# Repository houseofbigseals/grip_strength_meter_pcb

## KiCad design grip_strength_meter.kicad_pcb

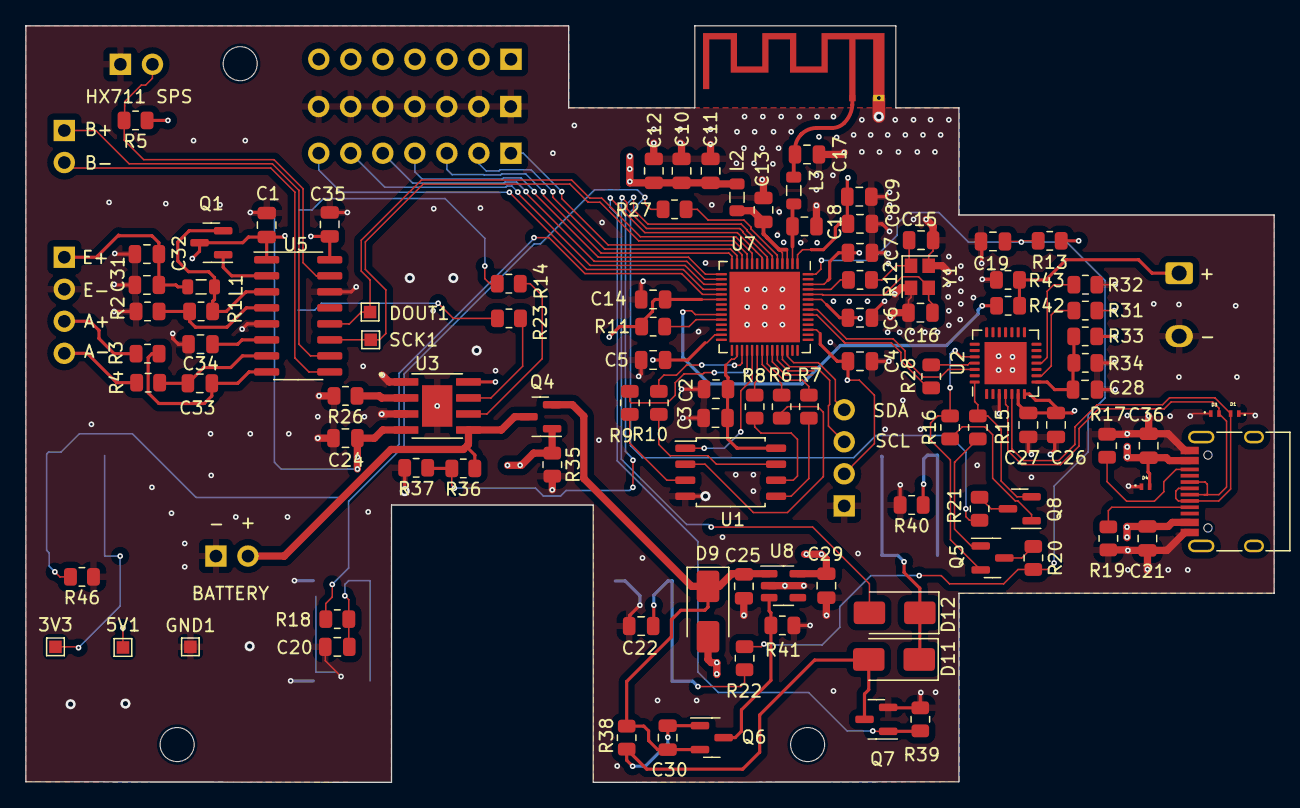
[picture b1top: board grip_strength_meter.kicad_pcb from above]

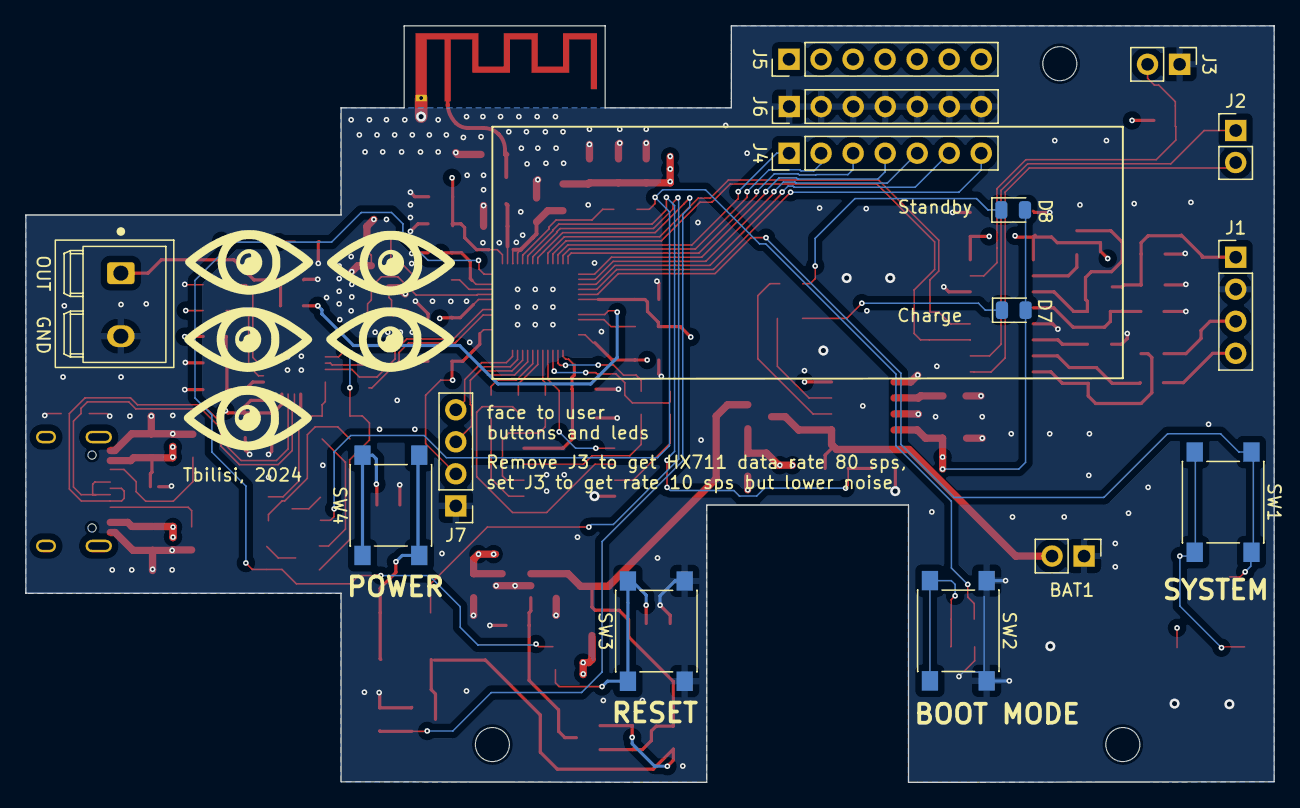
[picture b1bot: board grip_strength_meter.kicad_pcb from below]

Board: 4 copper layers, 99.0 x 60.0 mm, 122 parts (15 on the bottom side), 83 nets.

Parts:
3V3, 5V1: TestPoint; TestPoint_Pad_1.0x1.0mm
AE2: Antenna_Chip; Texas_SWRA117D_2.4GHz_Left
BAT1: Conn_01x02_Pin; PinHeader_1x02_P2.54mm_Vertical
C1, C2, C4, C5, C6, C7, C8, C11, C13, C14, C26, C30, C31, C33, C34: 100nF; C_0805_2012Metric
C3, C9, C10, C19: 1uF; C_0805_2012Metric
C12, C24, C28, C32, C35: 10uF; C_0805_2012Metric
C15, C16: 10pF; C_0805_2012Metric
C17: 1.2pF; C_0805_2012Metric
C18: 1.8pF; C_0805_2012Metric
C20, C22: 100 nF; C_0805_2012Metric
C21, C36: 5uF; C_0805_2012Metric
C25, C29: 2uF; C_0805_2012Metric
C27: 4.7uF; C_0805_2012Metric
D1, D3, D4: H5VL10B; DIODFN2_98X58X50L26X51N
D7: RED LED; LED_0805_2012Metric
D8: GREEN LED; LED_0805_2012Metric
D9, D11, D12: SS54; D_SMA
DOUT1: TestPoint; TestPoint_Pad_1.0x1.0mm
GND1: TestPoint; TestPoint_Pad_1.0x1.0mm
H1, H2, H3: MountingHole; MountingHole_2.7mm_M2.5_ISO7380
J1: Conn_01x04_Male; PinHeader_1x04_P2.54mm_Vertical
J2, J3: Conn_01x02_Male; PinHeader_1x02_P2.54mm_Vertical
J4, J5, J6: Conn_01x07_Pin; PinHeader_1x07_P2.54mm_Vertical
J7: Conn_01x04_Pin; PinHeader_1x04_P2.54mm_Vertical
L1: 3.3uH; L_0805_2012Metric
L2: 2nH; L_0805_2012Metric
L3: 2.4nH; L_0805_2012Metric
OUTPUT1: Screw_Terminal_01x02; screw-2-pin
Q1: SS8550; SOT-23
Q4, Q6: AO3401A; SOT-23
Q5, Q8: MMBT3904; SOT-23
Q7: AO3400A; SOT-23
R1, R5: 20K; R_0805_2012Metric
R2: 8.2K; R_0805_2012Metric
R3, R4, R40: 100R; R_0805_2012Metric
R6, R7, R8, R9, R10, R12, R18, R20, R21, R22: 0R; R_0805_2012Metric
R11, R13, R15, R16, R32, R36, R43, R46: 10K; R_0805_2012Metric
R14, R23: 1K; R_0805_2012Metric
R17, R19: 5K1; R_0805_2012Metric
R26: 1K5; R_0805_2012Metric
R27: 22R; R_0805_2012Metric
R28: 499R; R_0805_2012Metric
R31: 4K7; R_0805_2012Metric
R33: 24K; R_0805_2012Metric
R34: 47K; R_0805_2012Metric
R35, R38, R41: 100K; R_0805_2012Metric
R37, R42: 30K; R_0805_2012Metric
R39: 1M; R_0805_2012Metric
SCK1: TestPoint; TestPoint_Pad_1.0x1.0mm
SW1, SW2, SW3, SW4: SW_DPST; SW_Push_1P1T_NO_6x6mm_H9.5mm
U1: W25Q128JVS; SOIC-8_5.23x5.23mm_P1.27mm
U2: CP2102; QFN-28-1EP_5x5mm_P0.5mm_EP3.35x3.35mm
U3: TP4056; SOP127P600X175-9N
U5: HX711; SOP-16_3.9x9.9mm_P1.27mm
U7: ESP32-S2; QFN-56-1EP_7x7mm_P0.4mm_EP5.6x5.6mm
U8: TLV75733PDBV; SOT-23-5
USBC1: USB_C_Receptacle_USB2.0; USB_C_Receptacle_HRO_TYPE-C-31-M-12
Y1: Crystal_GND24; Crystal_SMD_2520-4Pin_2.5x2.0mm

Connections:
/3V3: 3V3.1, C1.1, C4.1, C5.1, C6.1, C7.1, C8.1, C9.1, C10.1, C11.1, C12.1, C14.1, C26.1, C27.1, C29.1, C35.1, J5.1, J5.2, J5.3, J5.4, J5.5, J5.6, J5.7, J7.2, L2.2, Q1.3 (E), R5.1, R11.2, R13.2, R31.1, SW1.2, U2.6 (VDD), U2.7 (VREGIN), U5.1 (VSUP), U5.16 (DVDD), U7.1 (VDDA), U7.20 (VDD3P3_RTC), U7.27 (VDD3P3_RTC_IO), U7.45 (VDD3P3_CPU), U7.51 (VDDA), U7.54 (VDDA), U8.5 (OUT)
/5V_USB: 5V1.1, C21.1, C24.1, C36.1, D4.2 (A2), D7.2 (A), D8.2 (A), D9.2 (A), Q4.1 (G), R33.2, R35.1, U3.4 (VCC), U3.8 (CE), USBC1.A4 (VBUS), USBC1.A9 (VBUS), USBC1.B4 (VBUS), USBC1.B9 (VBUS)
/CP2102_RX: R28.2, U2.25 (RXD)
/CP2102_TX: U2.26 (TXD), U7.49 (U0RXD/GPIO44)
/DOUT: DOUT1.1, U5.12 (DOUT), U7.10 (GPIO5/ADC1_CH4)
/DTR: Q8.2 (E), R15.2, U2.28 (~DTR)
/GPIO_BUTTON_CHECK: D12.2 (A), U7.7 (GPIO2/ADC1_CH1)
/GPIO_POWEROFF: Q7.1 (G), R39.1, U7.8 (GPIO3/ADC1_CH2)
/PD_SCK: SCK1.1, U5.11 (PD_SCK), U7.11 (GPIO6/ADC1_CH5)
/RTS: Q5.2 (E), R16.2, U2.24 (~RTS)
/V_BAT_MEASURE: R36.2, R37.1, U7.6 (GPIO1/ADC1_CH0)
/mcu_buttons_leds/CHIP_EN: C19.1, R13.1, R20.2, R22.2, U7.56 (CHIP_PU/RESET)
/mcu_buttons_leds/CIO0_BTN: R18.2, R21.2, R27.1
/mcu_buttons_leds/DAC_OUT: OUTPUT1.1, R42.2, R43.2
/mcu_buttons_leds/GPIO7: J4.1, U7.12 (GPIO7/ADC1_CH6)
/mcu_buttons_leds/GPIO8: J4.2, U7.13 (GPIO8/ADC1_CH7)
/mcu_buttons_leds/GPIO9: J4.3, U7.14 (GPIO9/ADC1_CH8)
/mcu_buttons_leds/GPIO10: J4.4, U7.15 (GPIO10/ADC1_CH9)
/mcu_buttons_leds/GPIO11: J4.5, U7.16 (GPIO11/ADC2_CH0)
/mcu_buttons_leds/GPIO12: J4.6, U7.17 (GPIO12/ADC2_CH1)
/mcu_buttons_leds/GPIO13: J4.7, U7.18 (GPIO13/ADC2_CH2)
/mcu_buttons_leds/GPIO14: R46.2, SW1.1, U7.19 (GPIO14/ADC2_CH3)
/mcu_buttons_leds/GPIO35: J7.3, U7.39 (GPIO35)
/mcu_buttons_leds/GPIO36: J7.4, U7.40 (GPIO36)
/mcu_buttons_leds/VDD_SPI: C2.1, C3.1, U1.8 (VCC), U7.30 (VDD_SPI)
/tp4056/POWER_EN: Q6.3 (D), R41.1, U8.3 (EN)
/tp4056/V_BAT: BAT1.2, Q4.3 (D), R36.1, U3.5 (BAT)
/usb_cp2102/USB_N: D1.2 (A2), U2.5 (D-), USBC1.A7 (D-), USBC1.B7 (D-)
/usb_cp2102/USB_P: D3.2 (A2), U2.4 (D+), USBC1.A6 (D+), USBC1.B6 (D+)
GND: AE2.2 (GND), BAT1.1, C1.2, C2.2, C3.2, C4.2, C5.2, C6.2, C7.2, C8.2, C9.2, C10.2, C11.2, C12.2, C13.2, C14.2, C15.2, C16.2, C17.2, C18.2, C19.2, C20.1, C21.2, C22.1, C24.2, C25.2, C26.2, C27.2, C28.2, C29.2, C31.2, C32.2, C34.2, C35.2, C36.2, D1.1 (A1), D3.1 (A1), D4.1 (A1), GND1.1, J1.2, J3.1, J6.1, J6.2, J6.3, J6.4, J6.5, J6.6, J6.7, J7.1, OUTPUT1.2, Q7.2 (S), R2.2, R17.2, R19.2, R26.2, R32.2, R34.1, R35.2, R37.2, R39.2, R40.2, R41.2, R43.1, R46.1, SW2.1, SW3.2, U1.4 (GND), U2.3 (GND), U2.29 (GND), U3.1 (TEMP), U3.3 (GND), U3.9 (EP), U5.5 (AGND), U5.14 (XI), U7.57 (GND), U8.2 (GND), USBC1.A1 (GND), USBC1.A12 (GND), USBC1.B1 (GND), USBC1.B12 (GND), Y1.2, Y1.4
unnamed: AE2.1 (FEED), C17.1, L3.1
unnamed: C13.1, L2.1, U7.3 (VDD3P3), U7.4 (VDD3P3)
unnamed: C15.1, R12.1, Y1.1
unnamed: C20.2, R18.1, SW2.2
unnamed: C22.2, R22.1, SW3.1
unnamed: D7.1 (K), R23.1
unnamed: D8.1 (K), R14.1
unnamed: C30.2, D11.2 (A), Q6.1 (G), Q7.3 (D), R38.2
unnamed: D11.1 (K), D12.1 (K), SW4.2
unnamed: C31.1, C32.1, J1.1, L1.1
unnamed: J1.3, R3.2
unnamed: J1.4, R4.2
unnamed: J2.1, U5.10 (INB+)
unnamed: J2.2, U5.9 (INB-)
unnamed: J3.2, R5.2, U5.15 (RATE)
unnamed: Q1.1 (B), U5.2 (BASE)
unnamed: L1.2, Q1.2 (C), R1.1, U5.3 (AVDD)
unnamed: Q5.1 (B), R15.1
unnamed: Q5.3 (C), R20.1
unnamed: Q8.1 (B), R16.1
unnamed: Q8.3 (C), R21.1
unnamed: R40.1, SW4.1
unnamed: R8.1, U1.6 (CLK)
unnamed: R7.1, U1.5 (DI(IO0))
unnamed: R6.1, U1.2 (DO(IO1))
unnamed: R9.1, U1.3 (IO2)
unnamed: R10.1, U1.7 (IO3)
unnamed: U1.1 (~CS), U7.33 (SPICS0/GPIO29)
unnamed: C28.1, R33.1, R34.2, U2.8 (VBUS)
unnamed: R31.2, U2.9 (~RST)
unnamed: R32.1, U2.11 (~SUSPEND)
unnamed: R26.1, U3.2 (PROG)
unnamed: R23.2, U3.7 (~CHRG)
unnamed: R14.2, U3.6 (~STDBY)
unnamed: C33.1, R3.1, U5.8 (INA+)
unnamed: C33.2, R4.1, U5.7 (INA-)
unnamed: C34.1, U5.6 (VBG)
unnamed: R1.2, R2.1, U5.4 (VFB)
unnamed: R27.2, U7.5 (GPIO0/BOOT)
unnamed: R42.1, U7.23 (GPIO17/ADC2_CH6/DAC_1)
unnamed: R11.1, U7.24 (GPIO18/ADC2_CH7/DAC_2)
unnamed: C18.1, L3.2, U7.2 (LNA_IN/RF)
unnamed: R8.2, U7.34 (SPICLK/GPIO30)
unnamed: R7.2, U7.36 (SPID/GPIO32)
unnamed: R10.2, U7.31 (SPIHD/GPIO27)
unnamed: R6.2, U7.35 (SPIQ/GPIO31)
unnamed: R9.2, U7.32 (SPIWP/GPIO28)
unnamed: R28.1, U7.48 (U0TXD/GPIO43)
unnamed: C16.1, U7.52 (XTAL_N), Y1.3
unnamed: R12.2, U7.53 (XTAL_P)
unnamed: R19.1, USBC1.A5 (CC1)
unnamed: R17.1, USBC1.B5 (CC2)
V_MIXED: C25.1, C30.1, D9.1 (K), Q4.2 (S), Q6.2 (S), R38.1, U8.1 (IN)

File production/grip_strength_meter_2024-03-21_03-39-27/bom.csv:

Designator,Footprint,Quantity,Value,LCSC Part #,Comment
"C1, C11, C13, C14, C2, C26, C30, C31, C33, C34, C4, C5, C6, C7, C8, C22",805,16,100nF,C28233,https://jlcpcb.com/partdetail/28983-CL21B104KCFNNNE/C28233
"C10, C19, C3, C9",805,4,1uF,C28323 ,https://jlcpcb.com/partdetail/29074-CL21B105KBFNNNE/C28323
"C12, C24, C28, C32, C35",805,5,10uF,C15850 ,https://jlcpcb.com/partdetail/16532-CL21A106KAYNNNE/C15850
"C15, C16",805,2,10pF,C913595,
C17,805,1,1.2pF,C565579,
C18,805,1,1.8pF,C318724,
"C21, C36",805,2,4.7uF,C1779 ,https://jlcpcb.com/partdetail/2131-CL21A475KAQNNNE/C1779
"C25, C29",805,2,2.2uF,C377773 ,https://jlcpcb.com/partdetail/350246-CL21A225KBQNNNE/C377773
C27,805,1,4.7uF,C1779 ,https://jlcpcb.com/partdetail/2131-CL21A475KAQNNNE/C1779
"D1, D3, D4",DIODFN2_98X58X50L26X51N,3,H5VL10B,C7420372 ,https://jlcpcb.com/parts/componentSearch?searchTxt=H5VL10B
"D11, D12, D9",SMA(DO-214AC),3,SS54,C7420369,https://jlcpcb.com/partdetail/Hongjiacheng-SS54/C7420369
,,,,,
,,,,,
L1,805,1,3.3uH,C307744,
L2,805,1,2.2nH,C251816 ,
L3,805,1,2.7nH,C578018,
Q1,SOT-23,1,SS8550,C8542 ,https://jlcpcb.com/partdetail/9037-SS8550Y2/C8542
"Q4, Q6",SOT-23,2,AO3401A,C15127 ,https://jlcpcb.com/partdetail/Alpha_OmegaSemicon-AO3401A/C15127
"Q5, Q8",SOT-23,2,MMBT3904,C20526,https://jlcpcb.com/partdetail/21237-MMBT3904/C20526
Q7,SOT-23,1,AO3400A,C20917 ,https://jlcpcb.com/partdetail/Alpha_OmegaSemicon-AO3400A/C20917
"R1, R5",805,2,20K,C4328,https://jlcpcb.com/partdetail/4735-0805W8F2002T5E/C4328
"R10, R12, R18, R20, R21, R22, R6, R7, R8, R9",805,10,0R,C17477,
"R11, R13, R15, R16, R36, R43, R46",805,7,10K,C17414,https://jlcpcb.com/partdetail/18102-0805W8F1002T5E/C17414
"R14, R23",805,2,1K,C17513 ,
"R17, R19",805,2,5K1,C27834 ,
R2,805,1,8.2K,C17828 ,
R26,805,1,1K5,C4310,
R27,805,1,22R,C17561 ,
R28,805,1,499R,C218597,
"R3, R4, R40",805,3,100R,C17408 ,
R31,805,1,4K7,C17673 ,
R33,805,1,24K,C17575,
R34,805,1,47K,C17713 ,
"R35, R38, R41",805,3,100K,C149504,
"R37, R42",805,2,30K,C17621 ,
R39,805,1,1M,C17514 ,
,,,,,
U1,SOIC-8_5.23x5.23mm_P1.27mm,1,W25Q128JVS,C97521 ,
U2,QFN-28-1EP_5x5mm_P0.5mm_EP3.35x3.35mm,1,CP2102,C6568 ,
U3,SOP127P600X175-9N,1,TP4056,C16581 ,
U5,SOP-16_3.9x9.9mm_P1.27mm,1,HX711,C6705483,
U7,QFN-56-1EP_7x7mm_P0.4mm_EP5.6x5.6mm,1,ESP32-S2,C2840995,
U8,SOT-23-5,1,TLV75733PDBV,C485517,
Y1,Crystal_SMD_2520-4Pin_2.5x2.0mm,1,X252040MMB4SI,C2885592,https://jlcpcb.com/partdetail/Yxc-X252040MMB4SI/C2885592

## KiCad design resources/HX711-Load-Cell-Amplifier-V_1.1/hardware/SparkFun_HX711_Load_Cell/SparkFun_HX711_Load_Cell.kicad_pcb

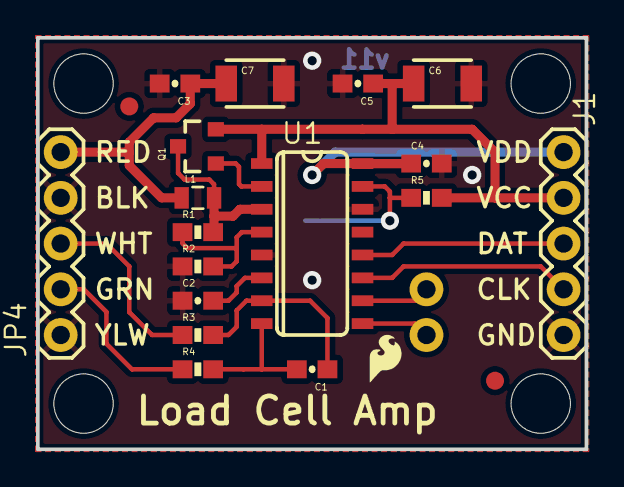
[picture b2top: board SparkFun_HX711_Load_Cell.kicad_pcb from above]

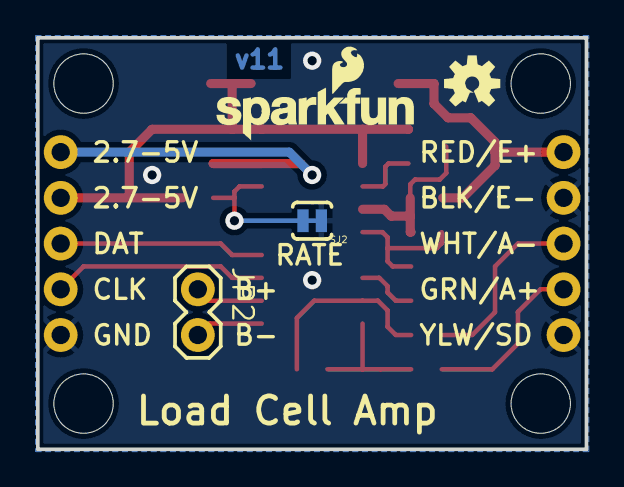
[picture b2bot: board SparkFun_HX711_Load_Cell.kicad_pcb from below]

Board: 2 copper layers, 30.5 x 22.9 mm, 30 parts (4 on the bottom side), 17 nets.

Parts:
C1, C2, C3, C4, C5: 0.1uF; 0603-CAP
C6, C7: 10uF; 1210
FID1, FID2: FIDUCIAL1X2; FIDUCIAL-1X2
FRAME1: FRAME-LETTER; CREATIVE_COMMONS
J1: 1X05
JP2: 1X02
JP4: 1X05
L1: 3.3uH; 0805
LOGO1: SFE_LOGO_NAME_FLAME.1_INCH; SFE_LOGO_NAME_FLAME_.1
LOGO3: SFE_LOGO_FLAME.1_INCH; SFE_LOGO_FLAME_.1
Q1: MMBT4403; SOT23-3
R1: 20k; 0603-RES
R2: 8.2K; 0603-RES
R3, R4: 100; 0603-RES
R5: 10K; 0603-RES
SJ2: PAD-JUMPER-2-NC_BY_TRACE_YES_SILK
STANDOFF1, STANDOFF2, STANDOFF3, STANDOFF4: STAND-OFF
U1: HX711; SO16
U7: OSHW-LOGOS; OSHW-LOGO-S
U$1: REVISION

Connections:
A+: JP4.2, R4.1
A-: JP4.3, R3.1
AVDD: C3.1, C7.1, JP4.5, L1.1
B+: JP2.1, U1.10
B-: JP2.2, U1.9
DAT: J1.3, U1.12
GND: C2.1, C3.2, C4.2, C5.2, C6.2, C7.2, J1.5, JP4.1, JP4.4, R2.1, SJ2.1, U1.5, U1.14
unnamed: R5.1, SJ2.2, U1.15
unnamed: C1.1, R3.2, U1.7
unnamed: C1.2, R4.2, U1.8
unnamed: Q1.1, U1.2
unnamed: L1.2, Q1.3, R1.2, U1.3
unnamed: R1.1, R2.2, U1.4
unnamed: C2.2, U1.6
SCK: J1.4, U1.11
VCC: C5.1, C6.1, J1.2, Q1.2, R5.2, U1.1
VDD: C4.1, J1.1, U1.16

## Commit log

2023-12-29 added esp32 base chip wiring
2023-12-30 added cp2102 schematics
2024-02-02 schematics almost finished
2024-02-14 pre pre production
2024-03-22 finished
2024-05-18 minor fix

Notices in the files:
parts and their libraries:
HTTPS://CREATIVECOMMONS.ORG/LICENSES/BY-SA/4.0
RELEASED UNDER THE CREATIVE COMMONS ATTRIBUTION SHARE-ALIKE 4.0 LICENSE
